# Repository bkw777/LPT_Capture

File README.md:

**NOTE: Only the top/default DB25_MicroUSB_BASIC version is tested and known good.**  
**All other versions are untested guesswork.**

# LPT Capture
Capture the output from a parallel printer port.

PCB: [PCBWAY](https://www.pcbway.com/project/shareproject/LPT_Capture.html)  
BOM: [DigiKey](https://www.digikey.com/short/j7w00c9c)

# Usage
Plug the device directly into the parallel printer port on a vintage computer.  
Connect a modern machine to the mico-usb port.

The device appears as a usb-serial adapter to the modern machine. Drivers are standard in any modern os or platform.  
Use any serial comm program like PuTTY or TeraTerm or minicom or gnu screen etc to read the COM port.  
It doesn't matter what baud rate you select in the comm program.

Print to the LPT port on the vintage machine.

Read the data from the COM port on the modern machine.

This device essentially takes the place of a printer, and only only impliments the basic original Centronics interface, no ieee1284 epp ecp bi-directional etc.

# Other Versions
The default "DB25 MicroUSB BASIC" version above is tested.  
None of the rest of these are tested yet.

[DB25 MicroUSB FANCY](README_DB25_MicroUSB_FANCY.md)  

[DB25 USBC BASIC](README_DB25_USBC_BASIC.md)  

[DB25 USBC FANCY](README_DB25_USBC_FANCY.md)  

[CN36 USBC FANCY](README_CN36_USBC_FANCY.md)

# Credits
[LptCap](https://www-user.tu-chemnitz.de/~heha/basteln/PC/LptCap/index.en.htm)

Differences:  
* KiCad instead of Eagle
* SSOP chip instead of QFN - easier to hand solder
* 0805 passives instead of 0603 - easier to hand solder
* microusb or usbc instead of miniusb
* mid-mount usb port - positions the plug in the center of the cable opening
* Snap-together backshell instead of screws & nuts
* VCCIO powered by VCC (5V) instead of 3V3OUT - LPT signals are 5V
* VBUS & VCC power conditioning per FT245R datasheet
* "fancy" versions impliment more signals (ONLINE, /SELIN, /RESET, /ERROR)
* CN36 version adds Peripheral Logic High and 5V power

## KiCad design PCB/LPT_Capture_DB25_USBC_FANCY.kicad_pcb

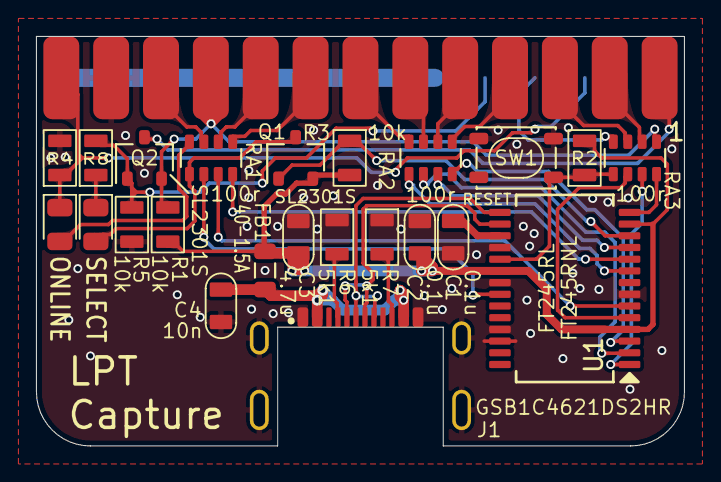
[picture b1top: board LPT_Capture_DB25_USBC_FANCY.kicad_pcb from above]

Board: 2 copper layers, 36.0 x 22.8 mm, 25 parts (0 on the bottom side), 37 nets.

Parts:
C1, C2: 0.1u; C_0805
C3: 4.7u; C_0805
C4: 10n; C_0805
FB1: 40-1.5A; L_0805
J1: GSB1C4621DS2HR; USBC_Receptacle_16pin_mid_mount
J2: DB25P064TXLF; DSUB-25_Male_EdgeMount_P2.77mm
LED1: ONLINE; LED_0805
LED2: SELECT; LED_0805
N1: 956-025-010R031; DSUB-25_Housing
Q1, Q2: SL2301S; SOT-23
R1, R2, R3, R4, R5, R8: 10k; R_0805
R6, R7: 5k1; R_0805
RA1, RA2, RA3: 100r; R_Array_Convex_4x0603
SW1: RESET; SW_SPST_PTS810
U1: FT245RL; SSOP-28

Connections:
/3v3: C1.2, U1.17 (3V3OUT)
/BUSY: J2.11, RA1.7 (R2.2)
/D0: RA3.3 (R3.1), U1.1 (D0)
/D1: RA3.2 (R2.1), U1.5 (D1)
/D2: RA2.4 (R4.1), U1.3 (D2)
/D3: RA2.3 (R3.1), U1.11 (D3)
/D4: RA2.2 (R2.1), U1.2 (D4)
/D5: RA2.1 (R1.1), U1.9 (D5)
/D6: RA1.4 (R4.1), U1.10 (D6)
/D7: RA1.3 (R3.1), U1.6 (D7)
/ON: LED2.2 (A), Q1.3 (D), RA1.1 (R1.1)
/ONLINE: J2.13, J2.15, LED1.1 (K), R4.1
/PD0: J2.2, RA3.6 (R3.2)
/PD1: J2.3, RA3.7 (R2.2)
/PD2: J2.4, RA2.5 (R4.2)
/PD3: J2.5, RA2.6 (R3.2)
/PD4: J2.6, RA2.7 (R2.2)
/PD5: J2.7, RA2.8 (R1.2)
/PD6: J2.8, RA1.5 (R4.2)
/PD7: J2.9, RA1.6 (R3.2)
/USB+: J1.A6 (D+), J1.B6 (D+), U1.15 (USBD+)
/USB-: J1.A7 (D-), J1.B7 (D-), U1.16 (USBD-)
/WR: RA3.4 (R4.1), U1.14 (WR)
/~INIT: J2.16, RA3.8 (R1.2)
/~PWREN: Q1.1 (G), R3.1, U1.12 (~PWREN)
/~RESET: R2.1, RA3.1 (R1.1), SW1.2, U1.19 (~RESET)
/~SELIN: J2.17, Q2.1 (G), R5.1, R8.2
/~STROBE: J2.1, Q2.3 (D)
/~STR: J2.10, Q2.2 (S), R1.1, RA3.5 (R4.2)
/~TXE: RA1.2 (R2.1), U1.22 (~TXE)
GND: C1.1, C2.2, C3.2, C4.2, J1.A1B12 (GND), J1.B1A12 (GND), J1.S (SHIELD), J2.12, J2.18, J2.19, J2.20, J2.21, J2.22, J2.23, J2.24, J2.25, R4.2, R5.2, R6.1, R7.1, SW1.1, U1.7 (GND1), U1.18 (GND2), U1.21 (GND3), U1.25 (AGND), U1.26 (TEST)
unnamed: J1.A5 (CC1), R6.2
unnamed: J1.B5 (CC2), R7.2
unnamed: LED1.2 (A), RA1.8 (R1.2)
unnamed: LED2.1 (K), R8.1
VBUS: C4.1, FB1.1, J1.A4B9 (VBUS), J1.B4A9 (VBUS)
VCC: C2.1, C3.1, FB1.2, Q1.2 (S), R1.2, R2.2, R3.2, U1.4 (VCCIO), U1.13 (~RD), U1.20 (VCC)

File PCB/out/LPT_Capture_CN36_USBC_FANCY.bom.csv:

"Reference","Value","Footprint","Qty","DNP","MPN","Description"
"C1,C2","0.1u","000_LOCAL:C_0805","2","","885012207045","CAP CER 0.1UF 16V X7R 0805"
"C3","4.7u","000_LOCAL:C_0805","1","","GRM21BR71C475KE51L","CAP CER 4.7UF 16V X7R 0805"
"C4","10n","000_LOCAL:C_0805","1","","885012207039","CAP CER 10000PF 16V X7R 0805"
"F1","500ma","000_LOCAL:F_1206","1","","0ZCJ0050AF2E","Resettable fuse, polymeric positive temperature coefficient, small symbol"
"FB1","40-1.5A","000_LOCAL:L_0805","1","","MH2029-400Y","FERRITE BEAD 40 OHM 0805 1LN"
"J1","GSB1C411101DS1HR","000_LOCAL:USBC_Receptacle_16pin_top_mount","1","","GSB1C411101DS1HR","USB 2.0-only 16P Type-C Receptacle connector"
"J2","112-036-213R001","000_LOCAL:Centronics_36F_RA_THT","1","","112-036-213R001","Centronics 36pin female 0.85 pitch"
"JP1","GND_USBSHLD","000_LOCAL:SolderJumper-2_P1.3mm_Bridged_RoundedPad1.0x1.5mm","1","","","Jumper, 2-pole, small symbol, bridged"
"JP2","GND_LPTSHLD","000_LOCAL:SolderJumper-2_P1.3mm_Bridged_RoundedPad1.0x1.5mm","1","","","Jumper, 2-pole, small symbol, bridged"
"JP3","USBSHLD_LPTSHLD","000_LOCAL:SolderJumper-2_P1.3mm_Bridged_RoundedPad1.0x1.5mm","1","","","Jumper, 2-pole, small symbol, bridged"
"LED1,LED2","LTL-307GLC","000_LOCAL:LED_D5.0mm","2","","LTL-307GLC","Light emitting diode"
"N1","Housing","000_LOCAL:Housing_CN36","1","","","Housing"
"Q1,Q2","SL2301S","000_LOCAL:SOT-23","2","","SL2301S","P-Channel MOSFET, SOT-23"
"R1,R2","5K1","000_LOCAL:R_0805","2","","RC0805FR-075K1L","RES 5K1 OHM 1% 1/8W 0805"
"R3,R4,R5,R6,R7,R8","10k","000_LOCAL:R_0805","6","","RC0805JR-0710KL","RES 10K OHM 5% 1/8W 0805"
"RA1,RA2,RA3,RA4","100r","000_LOCAL:R_Array_Convex_4x0603","4","","CAY16-101J4LF","RES ARRAY 4 RES 100 OHM 1206 convex"
"SW1","SW_DIP_x04","000_LOCAL:SW_DIP_SPST_Jumper_Dual_x04","1","","209-4MS","4x DIP Switch, Single Pole Single Throw (SPST) switch, small symbol"
"SW2","RESET","000_LOCAL:SW_SPST_PTS810","1","","RKB2SJM250SMTR LFS","Push button switch, generic, two pins"
"U1","FT245RL","000_LOCAL:SSOP-28","1","","FT245RNL","IC USB TO PARALLEL FIFO 28-SSOP"

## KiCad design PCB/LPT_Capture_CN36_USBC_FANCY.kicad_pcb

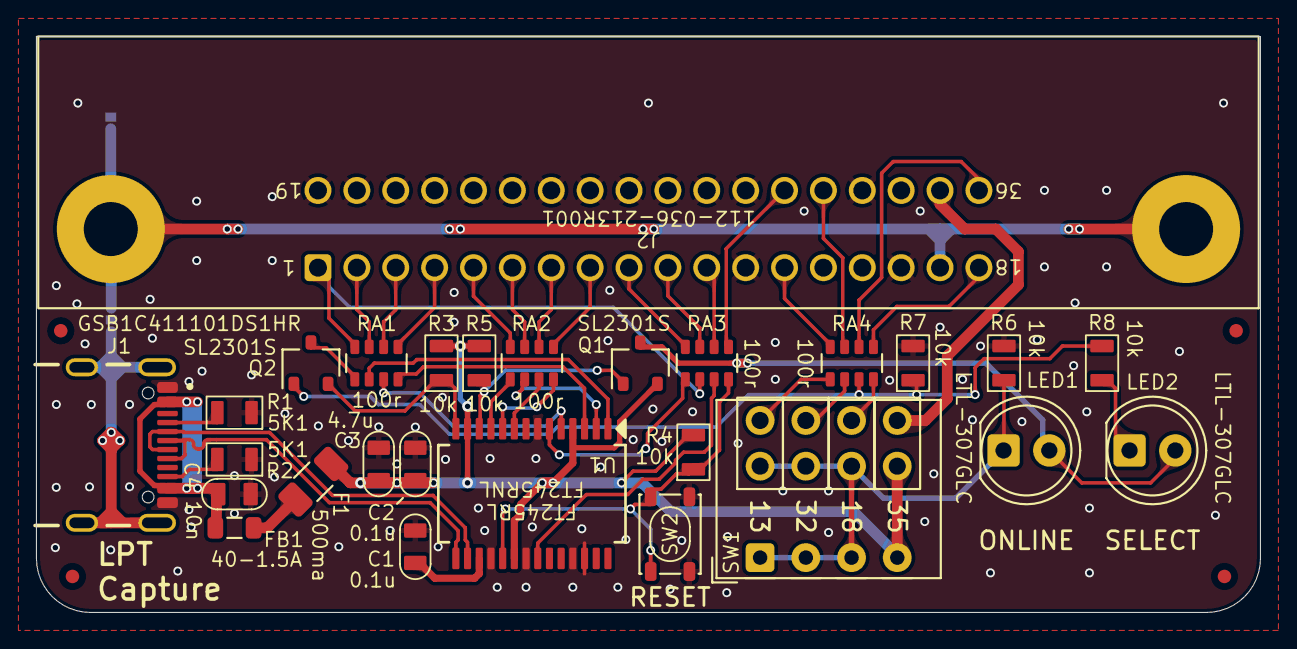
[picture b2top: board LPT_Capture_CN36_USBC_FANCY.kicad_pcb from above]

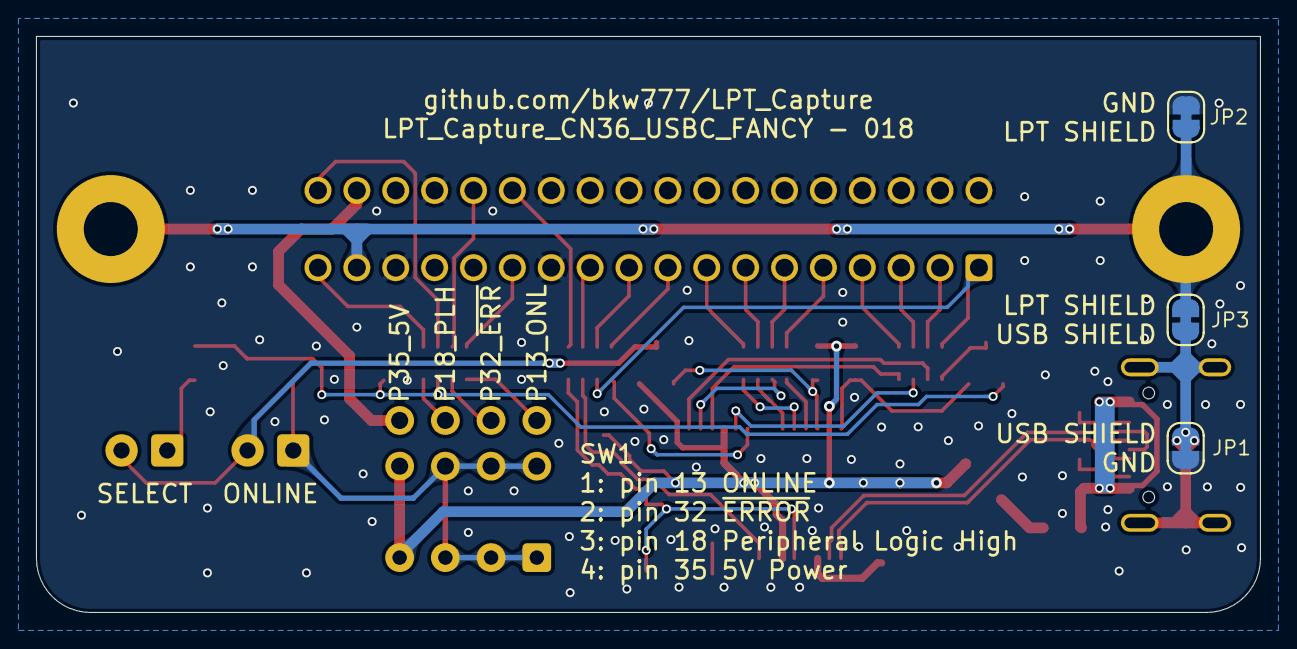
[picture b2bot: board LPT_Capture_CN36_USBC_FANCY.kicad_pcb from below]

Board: 2 copper layers, 68.0 x 32.0 mm, 31 parts (3 on the bottom side), 48 nets.

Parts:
C1, C2: 0.1u; C_0805
C3: 4.7u; C_0805
C4: 10n; C_0805
F1: 500ma; F_1206
FB1: 40-1.5A; L_0805
J1: GSB1C411101DS1HR; USBC_Receptacle_16pin_top_mount
J2: 112-036-213R001; Centronics_36F_RA_THT
JP1: GND_USBSHLD; SolderJumper-2_P1.3mm_Bridged_RoundedPad1.0x1.5mm
JP2: GND_LPTSHLD; SolderJumper-2_P1.3mm_Bridged_RoundedPad1.0x1.5mm
JP3: USBSHLD_LPTSHLD; SolderJumper-2_P1.3mm_Bridged_RoundedPad1.0x1.5mm
LED1, LED2: LTL-307GLC; LED_D5.0mm
N1: Housing; Housing_CN36
Q1, Q2: SL2301S; SOT-23
R1, R2: 5K1; R_0805
R3, R4, R5, R6, R7, R8: 10k; R_0805
RA1, RA2, RA3, RA4: 100r; R_Array_Convex_4x0603
SW1: SW_DIP_x04; SW_DIP_SPST_Jumper_Dual_x04
SW2: RESET; SW_SPST_PTS810
U1: FT245RL; SSOP-28

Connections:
/3v3: C1.1, U1.17 (3V3OUT)
/5V: J2.35, SW1.5
/BUSY: J2.11, RA3.6 (R3.2)
/D0: RA1.2 (R2.1), U1.1 (D0)
/D1: RA1.3 (R3.1), U1.5 (D1)
/D2: RA1.4 (R4.1), U1.3 (D2)
/D3: RA2.1 (R1.1), U1.11 (D3)
/D4: RA2.2 (R2.1), U1.2 (D4)
/D5: RA2.3 (R3.1), U1.9 (D5)
/D6: RA2.4 (R4.1), U1.10 (D6)
/D7: RA3.1 (R1.1), U1.6 (D7)
/ON: LED1.1 (K), R6.1, SW1.1, SW1.2, SW1.3
/ONLINE: J2.13, RA4.8 (R1.2)
/PD0: J2.2, RA1.7 (R2.2)
/PD1: J2.3, RA1.6 (R3.2)
/PD2: J2.4, RA1.5 (R4.2)
/PD3: J2.5, RA2.8 (R1.2)
/PD4: J2.6, RA2.7 (R2.2)
/PD5: J2.7, RA2.6 (R3.2)
/PD6: J2.8, RA2.5 (R4.2)
/PD7: J2.9, RA3.8 (R1.2)
/PLH: J2.18, RA4.5 (R4.2)
/PWREN: LED1.2 (A), LED2.2 (A), Q1.3 (D)
/USB+: J1.A6 (D+), J1.B6 (D+), U1.15 (USBD+)
/USB-: J1.A7 (D-), J1.B7 (D-), U1.16 (USBD-)
/WR: Q2.2 (S), R3.1, U1.14 (WR)
/sONL: RA4.1 (R1.1), SW1.8
/sPLH: RA4.4 (R4.1), SW1.6
/~ACK: J2.10, RA3.7 (R2.2)
/~ERROR: J2.32, RA4.7 (R2.2)
/~INIT: J2.31, RA3.5 (R4.2)
/~PWREN: Q1.1 (G), R5.1, U1.12 (~PWREN)
/~RESET: R4.1, RA3.4 (R4.1), SW2.2, U1.19 (~RESET)
/~SELIN: J2.36, RA4.6 (R3.2)
/~SEL: Q2.1 (G), R7.1, R8.2, RA4.3 (R3.1)
/~STROBE: J2.1, RA1.8 (R1.2), RA3.2 (R2.1)
/~STR: Q2.3 (D), RA1.1 (R1.1)
/~TXE: RA3.3 (R3.1), U1.22 (~TXE)
/~sERR: RA4.2 (R2.1), SW1.7
GND: C1.2, C2.2, C3.2, C4.2, J1.A1B12 (GND), J1.B1A12 (GND), J2.12, J2.16, J2.19, J2.20, J2.21, J2.22, J2.23, J2.24, J2.25, J2.26, J2.27, J2.28, J2.29, J2.30, J2.33, JP1.1 (A), JP2.1 (A), R1.1, R2.1, R6.2, R7.2, SW2.1, U1.7 (GND1), U1.18 (GND2), U1.21 (GND3), U1.25 (AGND), U1.26 (TEST)
LPT_SHIELD: J2.17, J2.S (Shield), JP2.2 (B), JP3.2 (B)
unnamed: F1.1, FB1.2
unnamed: J1.A5 (CC1), R1.2
unnamed: J1.B5 (CC2), R2.2
unnamed: LED2.1 (K), R8.1
USB_SHIELD: J1.S (SHIELD), JP1.2 (B), JP3.1 (A)
VBUS: C4.1, FB1.1, J1.A4B9 (VBUS), J1.B4A9 (VBUS)
VCC: C2.1, C3.1, F1.2, Q1.2 (S), R3.2, R4.2, R5.2, SW1.4, U1.4 (VCCIO), U1.13 (~RD), U1.20 (VCC)

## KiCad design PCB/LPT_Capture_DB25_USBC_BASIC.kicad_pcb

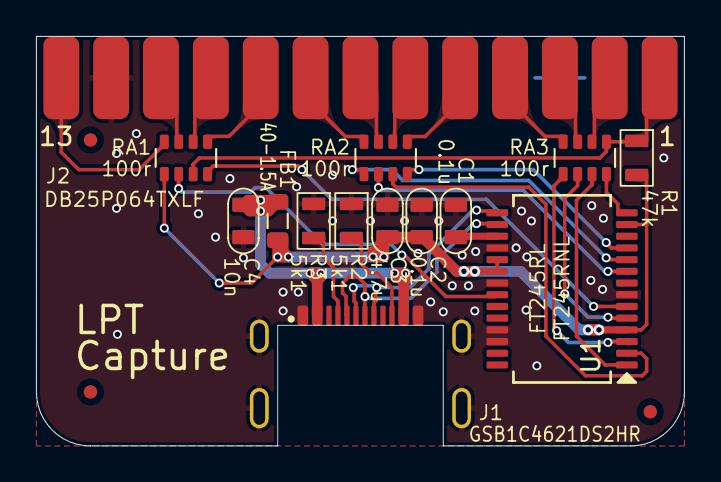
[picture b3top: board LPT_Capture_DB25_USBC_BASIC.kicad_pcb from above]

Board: 2 copper layers, 36.0 x 22.8 mm, 15 parts (0 on the bottom side), 31 nets.

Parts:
C1, C2: 0.1u; C_0805
C3: 4.7u; C_0805
C4: 10n; C_0805
FB1: 40-1.5A; L_0805
J1: GSB1C4621DS2HR; USBC_Receptacle_16pin_mid_mount
J2: DB25P064TXLF; DSUB-25_Male_EdgeMount_P2.77mm
N1: 956-025-010R031; DSUB-25_Housing
R1: 47k; R_0805
R2, R3: 5k1; R_0805
RA1, RA2, RA3: 100r; R_Array_Convex_4x0603
U1: FT245RL; SSOP-28

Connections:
/3v3: C1.1, U1.17 (3V3OUT)
/BUSY: J2.11, RA1.7 (R2.2)
/D0: RA3.3 (R3.1), U1.1 (D0)
/D1: RA3.2 (R2.1), U1.5 (D1)
/D2: RA3.1 (R1.1), U1.3 (D2)
/D3: RA2.4 (R4.1), U1.11 (D3)
/D4: RA2.3 (R3.1), U1.2 (D4)
/D5: RA2.2 (R2.1), U1.9 (D5)
/D6: RA2.1 (R1.1), U1.10 (D6)
/D7: RA1.4 (R4.1), U1.6 (D7)
/ONLINE: J2.13, RA1.8 (R1.2)
/PD0: J2.2, RA3.6 (R3.2)
/PD1: J2.3, RA3.7 (R2.2)
/PD2: J2.4, RA3.8 (R1.2)
/PD3: J2.5, RA2.5 (R4.2)
/PD4: J2.6, RA2.6 (R3.2)
/PD5: J2.7, RA2.7 (R2.2)
/PD6: J2.8, RA2.8 (R1.2)
/PD7: J2.9, RA1.5 (R4.2)
/USB+: J1.A6 (D+), J1.B6 (D+), U1.15 (USBD+)
/USB-: J1.A7 (D-), J1.B7 (D-), U1.16 (USBD-)
/WR: RA3.4 (R4.1), U1.14 (WR)
/~ACK: J2.10, RA1.6 (R3.2)
/~RESET: J2.15, J2.16
/~STROBE: J2.1, R1.1, RA1.3 (R3.1), RA3.5 (R4.2)
/~TXE: RA1.2 (R2.1), U1.22 (~TXE)
GND: C1.2, C2.2, C3.2, C4.2, J1.A1B12 (GND), J1.B1A12 (GND), J1.S (SHIELD), J2.12, J2.18, J2.19, J2.20, J2.21, J2.22, J2.23, J2.24, J2.25, R2.1, R3.1, U1.7 (GND1), U1.18 (GND2), U1.21 (GND3), U1.25 (AGND), U1.26 (TEST)
unnamed: J1.A5 (CC1), R3.2
unnamed: J1.B5 (CC2), R2.2
VBUS: C4.1, FB1.1, J1.A4B9 (VBUS), J1.B4A9 (VBUS)
VCC: C2.1, C3.1, FB1.2, R1.2, RA1.1 (R1.1), U1.4 (VCCIO), U1.13 (~RD), U1.19 (~RESET), U1.20 (VCC)

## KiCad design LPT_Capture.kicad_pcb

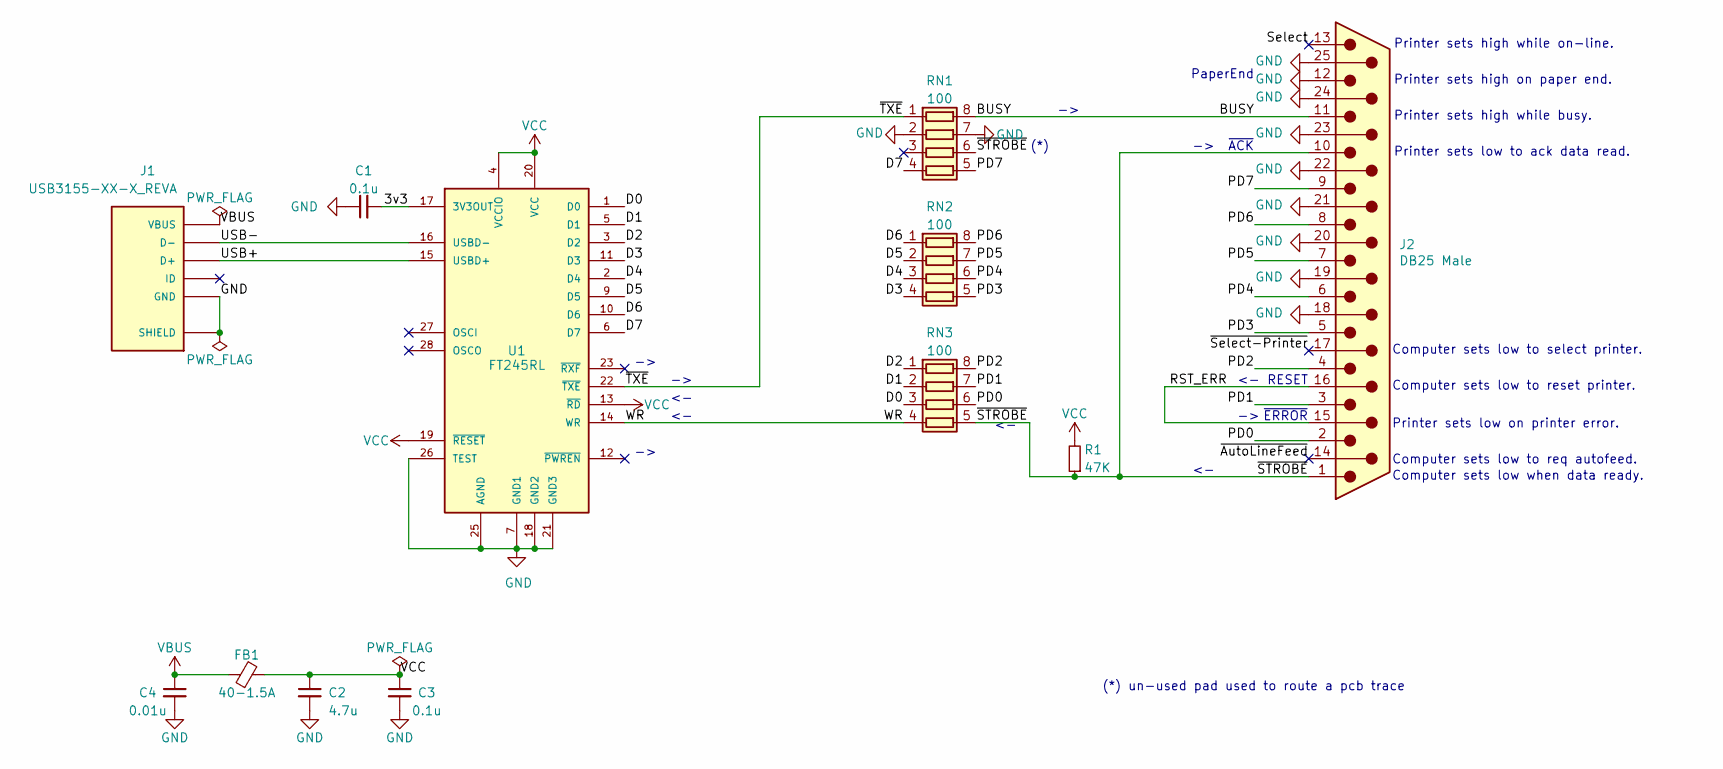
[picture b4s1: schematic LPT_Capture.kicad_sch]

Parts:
C1, C3: 0.1u; C_0805_2012Metric
C2: 4.7u; C_0805_2012Metric
C4: 0.01u; C_0805_2012Metric
FB1: 40-1.5A; L_0805_2012Metric
J1: USB3155-XX-X_REVA; GCT_USB3155-XX-X_REVA
J2: DB25 Male; DSUB-25_Male_EdgeMount_P2.77mm
R1: 47K; R_0805_2012Metric
RN1, RN2, RN3: 100; R_Array_Convex_4x0603
U1: FT245RL; SSOP-28_5.3x10.2mm_P0.65mm

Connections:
/3v3: C1.2, U1.17 (3V3OUT)
/BUSY: J2.11, RN1.8 (R1.2)
/D0: RN3.3 (R3.1), U1.1 (D0)
/D1: RN3.2 (R2.1), U1.5 (D1)
/D2: RN3.1 (R1.1), U1.3 (D2)
/D3: RN2.4 (R4.1), U1.11 (D3)
/D4: RN2.3 (R3.1), U1.2 (D4)
/D5: RN2.2 (R2.1), U1.9 (D5)
/D6: RN2.1 (R1.1), U1.10 (D6)
/D7: RN1.4 (R4.1), U1.6 (D7)
/PD0: J2.2, RN3.6 (R3.2)
/PD1: J2.3, RN3.7 (R2.2)
/PD2: J2.4, RN3.8 (R1.2)
/PD3: J2.5, RN2.5 (R4.2)
/PD4: J2.6, RN2.6 (R3.2)
/PD5: J2.7, RN2.7 (R2.2)
/PD6: J2.8, RN2.8 (R1.2)
/PD7: J2.9, RN1.5 (R4.2)
/RST_ERR: J2.15, J2.16
/Select: J2.13
/USB+: J1.3 (D+), U1.15 (USBD+)
/USB-: J1.2 (D-), U1.16 (USBD-)
/WR: RN3.4 (R4.1), U1.14 (WR)
/~AutoLineFeed: J2.14
/~STROBE: J2.1, J2.10, R1.1, RN1.6 (R3.2), RN3.5 (R4.2)
/~Select-Printer: J2.17
/~TXE: RN1.1 (R1.1), U1.22 (~TXE)
GND: C1.1, C2.2, C3.2, C4.2, J1.5 (GND), J1.S (SHIELD), J2.12, J2.18, J2.19, J2.20, J2.21, J2.22, J2.23, J2.24, J2.25, RN1.2 (R2.1), RN1.7 (R2.2), U1.7 (GND1), U1.18 (GND2), U1.21 (GND3), U1.25 (AGND), U1.26 (TEST)
VBUS: C4.1, FB1.1, J1.1 (VBUS)
VCC: C2.1, C3.1, FB1.2, R1.2, U1.4 (VCCIO), U1.13 (~RD), U1.19 (~RESET), U1.20 (VCC)

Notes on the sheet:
Printer sets high while on-line.
Computer sets low to reset printer.
RESET
Printer sets high on paper end.
(*)
~{ERROR}
Printer sets high while busy.
Computer sets low to req autofeed.
Computer sets low to select printer.
PaperEnd
(*) un-used pad used to route a pcb trace
Printer sets low on printer error.
Computer sets low when data ready.
Printer sets low to ack data read.
~{ACK}

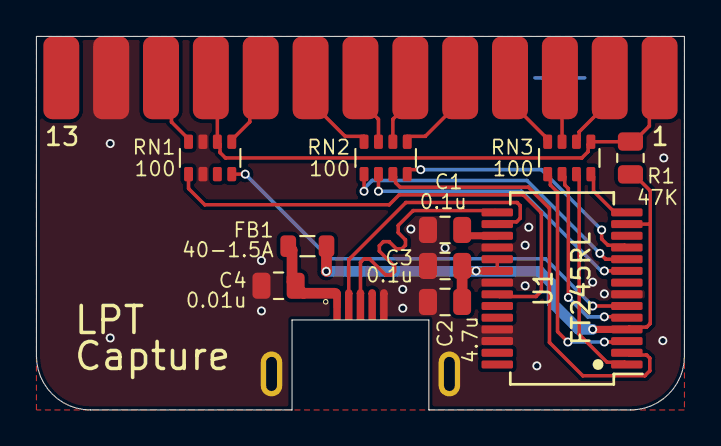
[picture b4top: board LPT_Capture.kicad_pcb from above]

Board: 2 copper layers, 36.0 x 20.8 mm, 12 parts (0 on the bottom side), 27 nets.

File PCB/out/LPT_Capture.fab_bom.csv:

"Reference","Value","Datasheet","Footprint","Qty","DNP","MPN","Description"
"C1,C3","100n","datasheets/885012207045.pdf","000_LOCAL:C_0805","2","","885012207045","CAP CER 0.1UF 16V X7R 0805"
"C2","4.7u","datasheets/GRM21BR71C475KE51-01.pdf","000_LOCAL:C_0805","1","","GRM21BR71C475KE51L","CAP CER 4.7UF 16V X7R 0805"
"C4","10n","datasheets/885012207039.pdf","000_LOCAL:C_0805","1","","885012207039","CAP CER 10000PF 16V X7R 0805"
"FB1","40-1.5A","datasheets/mh.pdf","000_LOCAL:L_0805","1","","MH2029-400Y","FERRITE BEAD 40 OHM 0805 1LN"
"J1","USB3155-XX-X_REVA","datasheets/usb3155.pdf","000_LOCAL:GCT_USB3155-XX-X_REVA","1","","USB3155-30-A","MICRO B SKT, HORIZONTAL MID SMT"
"J2","DB25 Male","datasheets/ASS_4884_CO.pdf","000_LOCAL:DSUB-25_Male_EdgeMount_P2.77mm","1","","A-DS 25 LL/Z","CONN D-SUB PLUG 25POS SLDR CUP"
"N1","DB25_backshell","datasheets/mhccovxx-sn-xx.pdf","000_LOCAL:db25_backshell","1","","MHCCOV-25-SN-LG","25 WAY D-SUB HOOD PLASTIC TOP EN"
"R1","47k","~","000_LOCAL:R_0805","1","","RC0805JR-0747KL","RES 47K OHM 5% 1/8W 0805"
"RA1,RA2,RA3","100","datasheets/CATCAY.pdf","000_LOCAL:R_Array_Convex_4x0603","3","","CAY16-101J4LF","RES ARRAY 4 RES 100 OHM 1206 convex"
"U1","FT245RL","datasheets/FT245R.pdf","000_LOCAL:SSOP-28","1","","FT245RL","IC USB TO PARALLEL FIFO 28-SSOP"

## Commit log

2021-06-05 initial
2021-06-05 link to buy pcb
2021-06-06 layout fine tuning
2021-06-07 tie select high
2021-06-08 small layout tweaks
2021-06-09 inverted centered usb jack
2021-06-09 readme
2021-06-10 db25 solder cups
2021-06-16 v004 rn footprints, add fb1 c3 c4
2021-06-16 bom & readme
2021-06-16 render
2021-06-16 more available fb1 in bom
2021-06-22 minor layout nudges
2021-06-28 better usb port attachment
2021-06-29 v008, better usb port
2021-06-29 version silkscreen
2021-06-30 disconnect Select
2023-01-28 kicad 6, minor layout tweaks, ft245rl symbol
2023-09-11 minor routing and silkscreen touch ups
2023-09-12 minor routing straighten
2024-05-15 add ONLINE & /RESET
2024-05-20 kicad8
2024-06-25 caps units, sch clutter
2024-08-31 add MPN to symbols, export fab_bom & centroid
2024-08-31 pics
2025-11-19 double vias on power
2025-11-20 pfet invert for online, bom
2025-12-01 add /SELECT
2025-12-01 update eol FT245R to FT245RN
2025-12-01 component library & models
2025-12-01 update bom
2025-12-03 USBC
2025-12-03 add another backshell pn
2025-12-03 part numbers notes
2025-12-03 silkscreen
2025-12-04 pulldown /SELIN
2025-12-04 vcc fewer vias, readme
2025-12-04 sch backshell comment
2025-12-04 resave
2025-12-05 cleanup symb & footp libs, add ONLINE
2025-12-10 sch notes compatible db25 parts
2025-12-10 strobe>ack via unused 100r
2025-12-11 readme other branches
2025-12-12 pull db25_usbc_basic into main
2025-12-12 pull db25_microusb_fancy into main
2025-12-12 fix db25_microusb_fancy filenames, pull db25_usbc_fancy into main
2025-12-12 pull c36_usbc_fancy into main
2025-12-12 README_DB25_MicroUSB_FANCY.md links
2025-12-12 renders
2025-12-12 centronics control flow arrows
2025-12-13 diff pair len match
2025-12-13 rename Centronics to CN36
2025-12-14 basic cover for CN36
2025-12-14 begin fancy cn36 cover
2025-12-14 cn36 tiny repositions
2025-12-15 cn36 cover
2025-12-16 varied cn36 models
2025-12-17 datasheets
2025-12-18 cn36 screwless snap-on full shell cover
2025-12-19 cn36: board dims, leds, housing
2025-12-20 cn36 cover shape
2025-12-20 cn36: missing datasheet, add RA4, refactor parts of cover scad
2025-12-20 cn36 readme
2025-12-22 cn36 add F1 SW1
2025-12-22 filenames
2025-12-22 reference material
2025-12-24 cn36 add jp1,2,3
2025-12-24 cn36 add R8 current limit led when /SELIN driven low
2025-12-25 db25-usbc-fancy add R8 current limit led when /SELIN driven low
2025-12-25 db25-microusb-fancy add R6 current limit led when /SELIN driven low
2025-12-26 cn36 dip sw and housing
2025-12-29 cn36 cover customizer
2025-12-31 notes
2026-03-26 cover scad include vs use
2026-03-26 fancy versions - prevent backfeed through online led
2026-03-26 cn36 ground paths around sw1
2026-03-28 cn36 add reset button
2026-04-18 DB25_USBC_FANCY add reset button

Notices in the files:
LPT_Capture.kicad_pcb:
CC-BY-SA
